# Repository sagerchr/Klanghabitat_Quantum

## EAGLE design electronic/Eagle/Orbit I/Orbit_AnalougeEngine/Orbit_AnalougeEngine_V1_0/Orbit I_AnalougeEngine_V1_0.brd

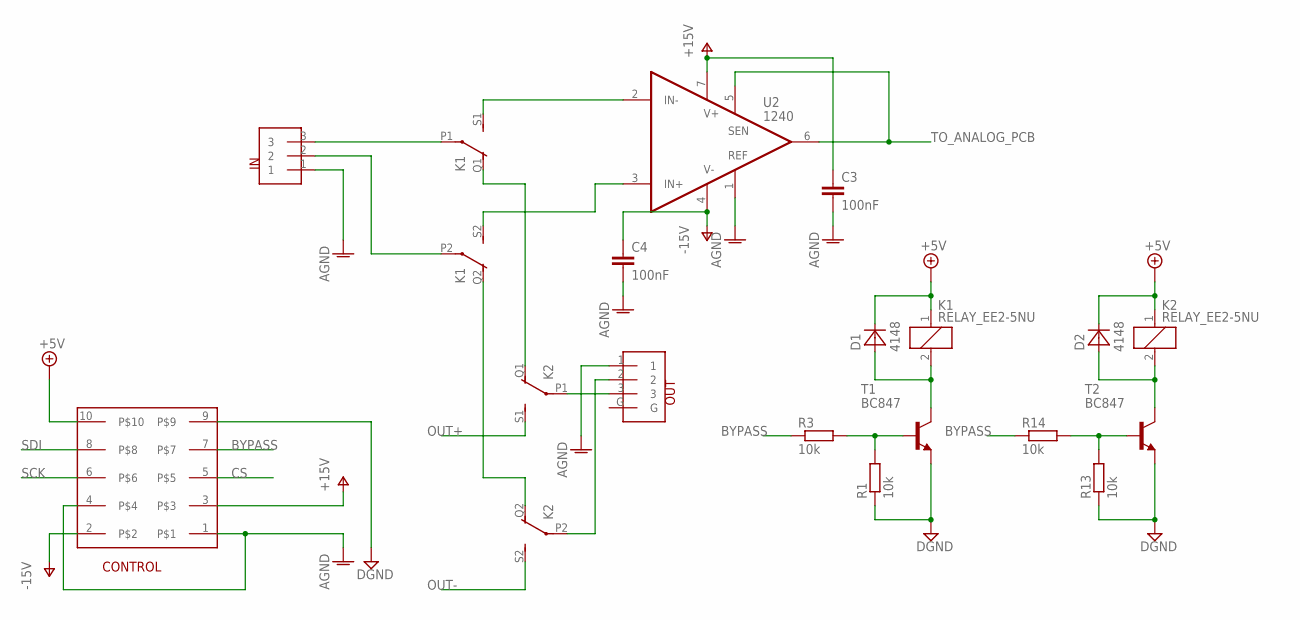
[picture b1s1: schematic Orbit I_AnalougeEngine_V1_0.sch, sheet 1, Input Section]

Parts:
C3, C4: 100nF; C0603
CONTROL: 10PIN_HEADER_SMD; 87832-10
D1, D2: 4148; SOD323-R
IN: NEUTRIK_NC3FAH
K1, K2: RELAY_EE2-5NU; 351
OUT: NEUTRIK_NC3MAH
R1, R3, R13, R14: 10k; R0805
T1, T2: BC847; SOT23
U2: 1240; SO08

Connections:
+5V: CONTROL.10, D1.C, D2.C, K1.1, K2.1
AGND: C3.2, C4.2, CONTROL.1, CONTROL.4, IN.1, OUT.1, U2.1 (REF); also elsewhere on the board
BYPASS: CONTROL.7, R3.1, R14.1
CS: CONTROL.5; also elsewhere on the board
DGND: CONTROL.9, R1.1, R13.1, T1.2 (E), T2.2 (E); also elsewhere on the board
unnamed: K1.S1 (S), U2.2 (IN-)
unnamed: K1.S2 (S), U2.3 (IN+)
unnamed: D2.A, K2.2, T2.3 (C)
unnamed: R13.2, R14.2, T2.1 (B)
unnamed: D1.A, K1.2, T1.3 (C)
unnamed: K1.Q1 (O), K2.Q1 (O)
unnamed: R1.2, R3.2, T1.1 (B)
unnamed: K1.Q2 (O), K2.Q2 (O)
unnamed: IN.2, K1.P2
unnamed: IN.3, K1.P1
unnamed: K2.P2, OUT.2
unnamed: K2.P1, OUT.3
OUT+: K2.S1 (S); also elsewhere on the board
OUT-: K2.S2 (S); also elsewhere on the board
SCK: CONTROL.6; also elsewhere on the board
SDI: CONTROL.8; also elsewhere on the board
TO_ANALOG_PCB: U2.5 (SEN), U2.6 (OUT); also elsewhere on the board
V+: C3.1, CONTROL.3, U2.7 (V+); also elsewhere on the board
V-: C4.1, CONTROL.2, U2.4 (V-); also elsewhere on the board

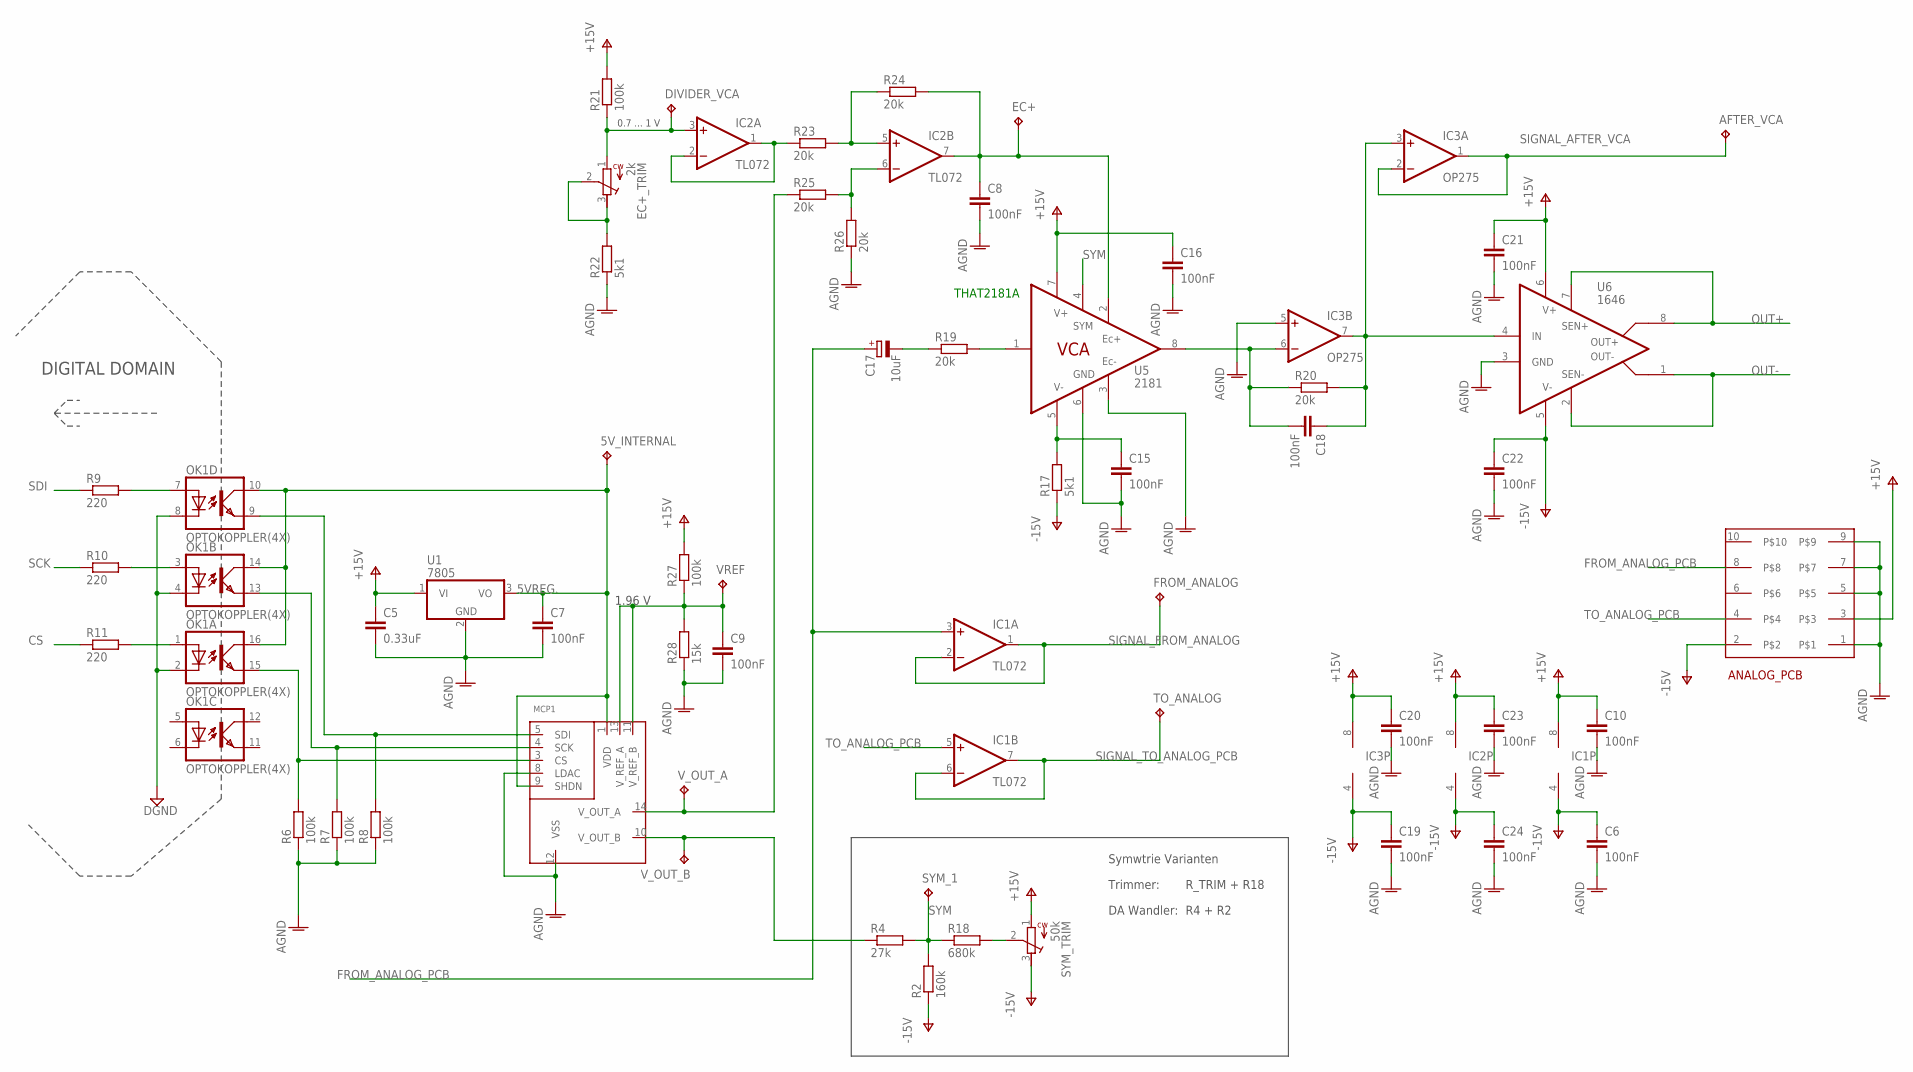
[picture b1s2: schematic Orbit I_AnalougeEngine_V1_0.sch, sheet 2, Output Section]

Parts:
5V_INTERNAL: TPTHT; THT_PIN
AFTER_VCA: TPTHT; THT_PIN
ANALOG_PCB: 10PIN_HEADER_SMD; 87832-10
C5: 0.33uF; C0603
C6, C7, C8, C9, C10, C15, C16, C18, C19, C20, C21, C22, C23, C24: 100nF; C0603
C17: 10uF; 153CLV-0605
DIVIDER_VCA: TPTHT; THT_PIN
EC+: TPTHT; THT_PIN
EC+_TRIM: 2k; RTRIM4G/J
FROM_ANALOG: TPTHT; THT_PIN
IC1, IC2: TL072; SOIC8
IC3: OP275; SOIC8
MCP1: MCP4922; SOIC16
OK1: OPTOKOPPLER(4X); SOIC16
R2: 160k; R0805
R4: 27k; R0805
R6, R7, R8, R21, R27: 100k; R0805
R9, R10, R11: 220; R0805
R17, R22: 5k1; R0805
R18: 680k; R0805
R19, R20, R23, R24, R25, R26: 20k; R0805
R28: 15k; R0805
SYM_1: TPTHT; THT_PIN
SYM_TRIM: 50k; RTRIM4G/J
TO_ANALOG: TPTHT; THT_PIN
U1: 7805; TO252
U5: 2181; SO08
U6: 1646; SO08
VREF: TPTHT; THT_PIN
V_OUT_A: TPTHT; THT_PIN
V_OUT_B: TPTHT; THT_PIN

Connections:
5VREG.: 5V_INTERNAL.P$1, C7.1, MCP1.1 (VDD), MCP1.9 (SHDN), OK1.10 (COL), OK1.14 (COL), OK1.16 (COL), U1.3 (VO)
AGND: ANALOG_PCB.1, ANALOG_PCB.5, ANALOG_PCB.7, ANALOG_PCB.9, C5.2, C6.2, C7.2, C8.2, C9.2, C10.2, C15.2, C16.2, C19.2, C20.2, C21.2, C22.2, C23.2, C24.2, IC3.5 (+IN), MCP1.8 (LDAC), MCP1.12 (VSS), R6.1, R7.1, R8.1, R22.1, R26.1, R28.1, U1.2 (GND), U5.3 (EC-), U5.6 (GND), U6.3 (GND); also elsewhere on the board
CS: R11.1; also elsewhere on the board
DGND: OK1.2 (C), OK1.4 (C), OK1.8 (C); also elsewhere on the board
FROM_ANALOG_PCB: ANALOG_PCB.8, C17.+, IC1.3 (+IN)
unnamed: C17.-, R19.1
unnamed: MCP1.3 (CS), OK1.15 (EMIT), R6.2
unnamed: MCP1.4 (SCK), OK1.13 (EMIT), R7.2
unnamed: MCP1.5 (SDI), OK1.9 (EMIT), R8.2
unnamed: OK1.7 (A), R9.2
unnamed: OK1.3 (A), R10.2
unnamed: OK1.1 (A), R11.2
unnamed: MCP1.10 (V_OUT_B), R4.1, V_OUT_B.P$1
unnamed: R18.2, SYM_TRIM.2
unnamed: C15.1, R17.2, U5.5 (V-)
unnamed: C18.2, IC3.6 (-IN), R20.1, U5.8 (OUT)
unnamed: C18.1, IC3.3 (+IN), IC3.7 (OUT), R20.2, U6.4 (IN)
unnamed: R19.2, U5.1 (IN)
unnamed: DIVIDER_VCA.P$1, EC+_TRIM.1, IC2.3 (+IN), R21.1
unnamed: IC2.1 (OUT), IC2.2 (-IN), R23.1
unnamed: IC2.5 (+IN), R23.2, R24.1
unnamed: C8.1, EC+.P$1, IC2.7 (OUT), R24.2, U5.2 (EC+)
unnamed: IC2.6 (-IN), R25.2, R26.2
unnamed: EC+_TRIM.2, EC+_TRIM.3, R22.2
unnamed: MCP1.14 (V_OUT_A), R25.1, V_OUT_A.P$1
unnamed: C9.1, MCP1.11 (V_REF_B), MCP1.13 (V_REF_A), R27.1, R28.2, VREF.P$1
OUT+: U6.7 (SEN+), U6.8 (OUT+); also elsewhere on the board
OUT-: U6.1 (OUT-), U6.2 (SEN-); also elsewhere on the board
SCK: R10.1; also elsewhere on the board
SDI: R9.1; also elsewhere on the board
SIGNAL_AFTER_VCA: AFTER_VCA.P$1, IC3.1 (OUT), IC3.2 (-IN)
SIGNAL_FROM_ANALOG: FROM_ANALOG.P$1, IC1.1 (OUT), IC1.2 (-IN)
SIGNAL_TO_ANALOG_PCB: IC1.6 (-IN), IC1.7 (OUT), TO_ANALOG.P$1
SYM: R2.2, R4.2, R18.1, SYM_1.P$1, U5.4 (SYM)
TO_ANALOG_PCB: ANALOG_PCB.4, IC1.5 (+IN); also elsewhere on the board
V+: ANALOG_PCB.3, C5.1, C10.1, C16.1, C20.1, C21.1, C23.1, IC1.8 (V+), IC2.8 (V+), IC3.8 (V+), R21.2, R27.2, SYM_TRIM.1, U1.1 (VI), U5.7 (V+), U6.6 (V+); also elsewhere on the board
V-: ANALOG_PCB.2, C6.1, C19.1, C22.1, C24.1, IC1.4 (V-), IC2.4 (V-), IC3.4 (V-), R2.1, R17.1, SYM_TRIM.3, U6.5 (V-); also elsewhere on the board

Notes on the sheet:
THAT2181A
0.7 ... 1 V
1.96 V
DIGITAL DOMAIN
Symwtrie Varianten
Trimmer:
R_TRIM + R18
DA Wandler:
R4 + R2

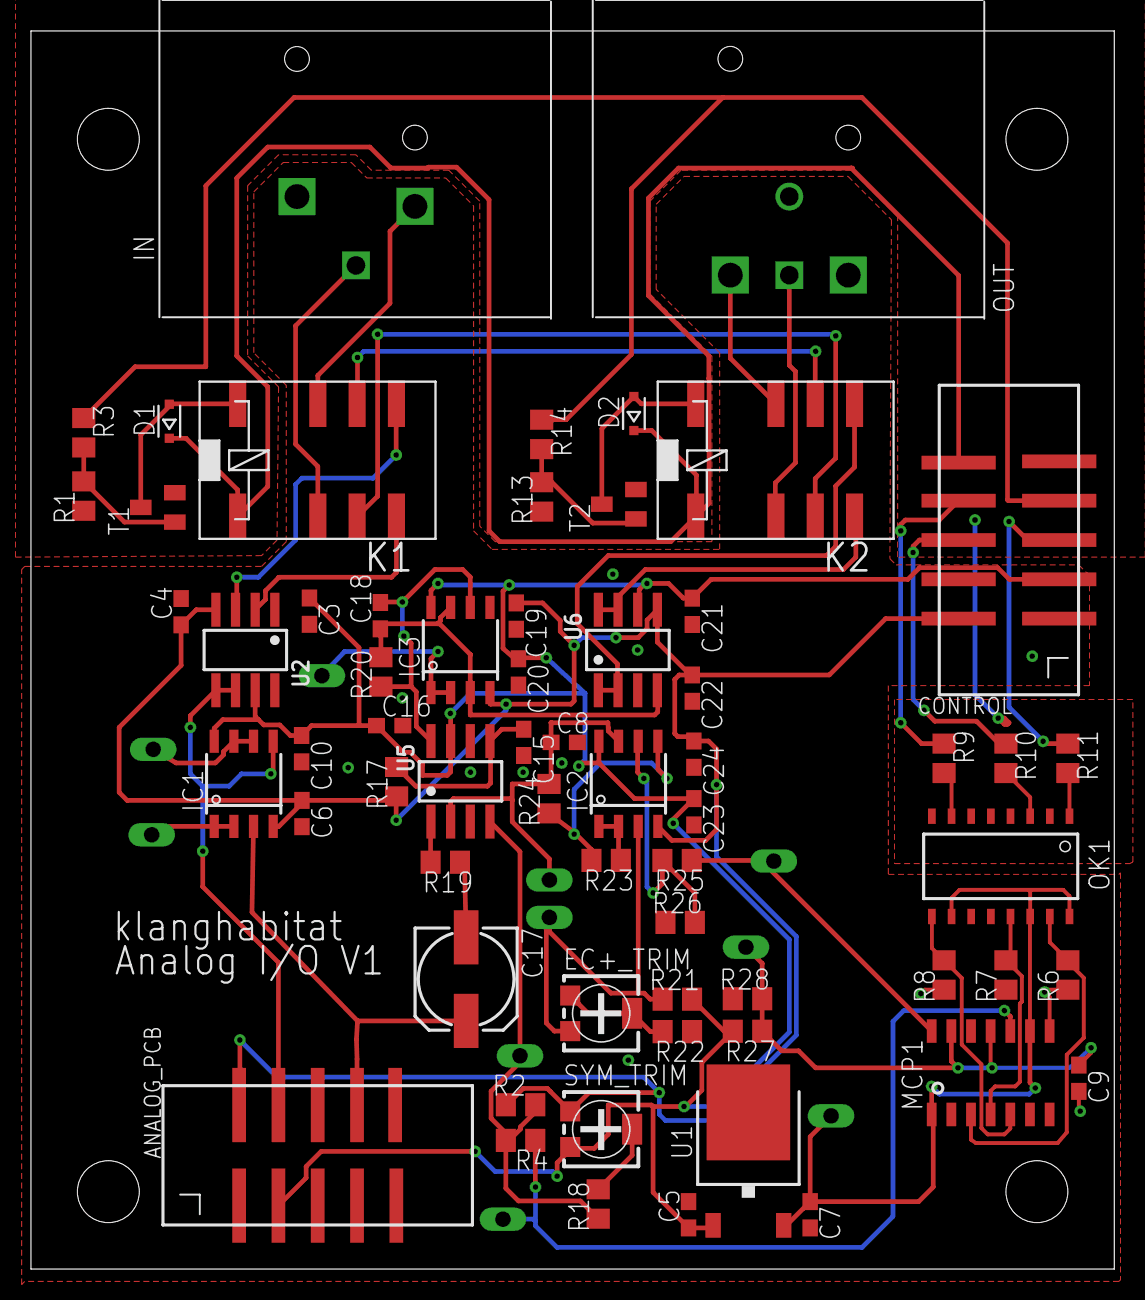
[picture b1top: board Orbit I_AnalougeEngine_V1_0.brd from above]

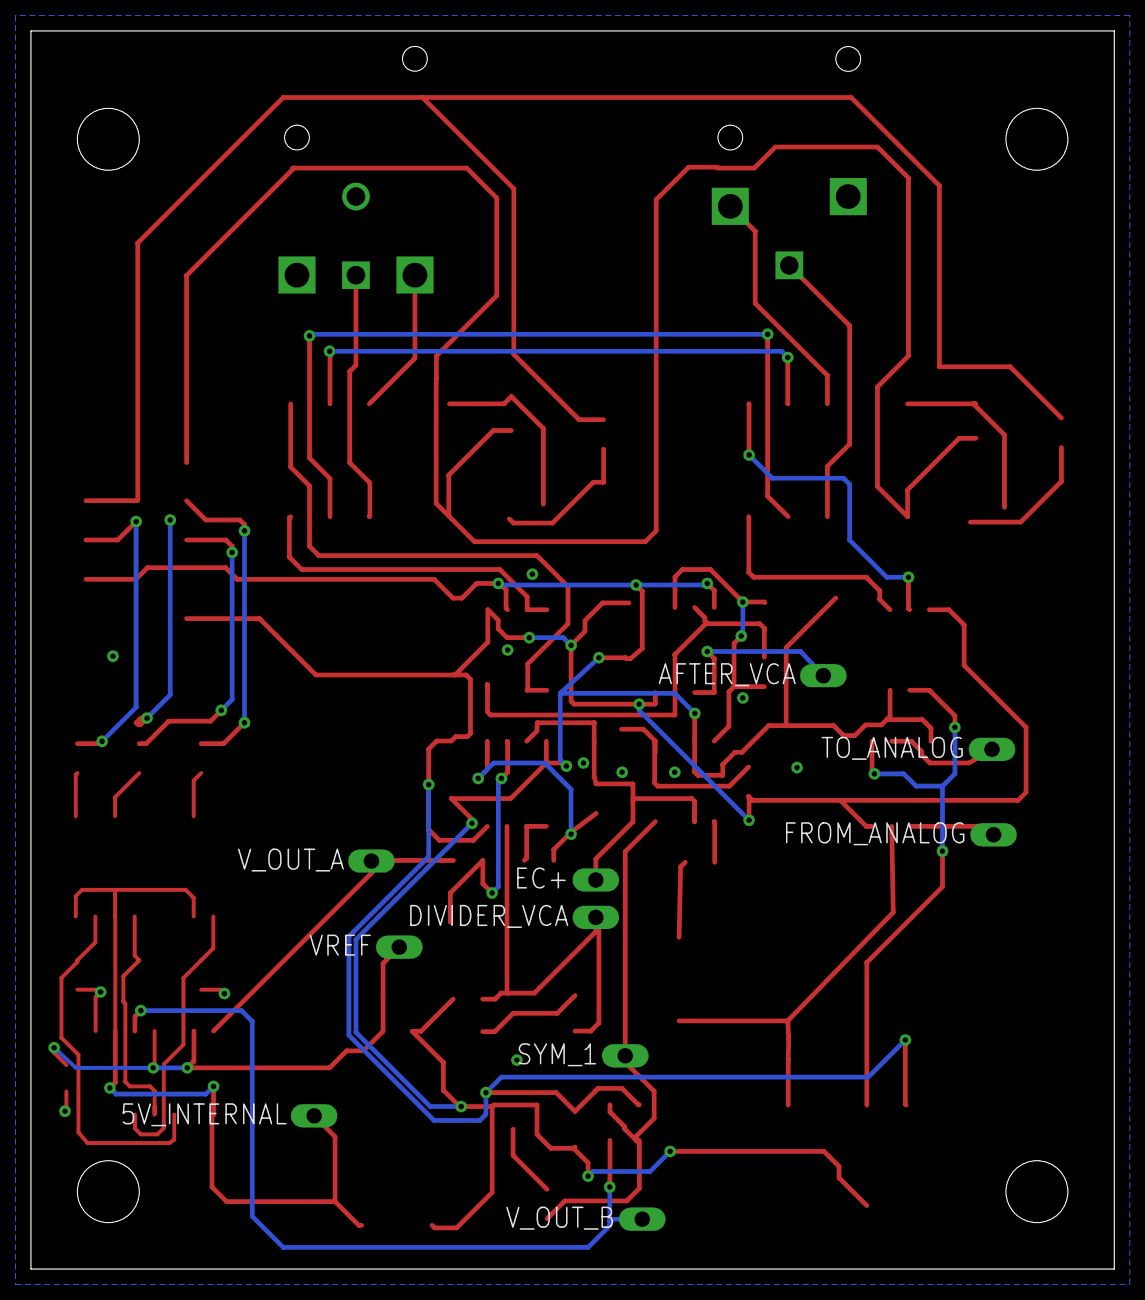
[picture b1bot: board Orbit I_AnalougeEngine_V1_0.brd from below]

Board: 2 copper layers, 70.0 x 80.0 mm, 73 parts (10 on the bottom side), 51 nets.

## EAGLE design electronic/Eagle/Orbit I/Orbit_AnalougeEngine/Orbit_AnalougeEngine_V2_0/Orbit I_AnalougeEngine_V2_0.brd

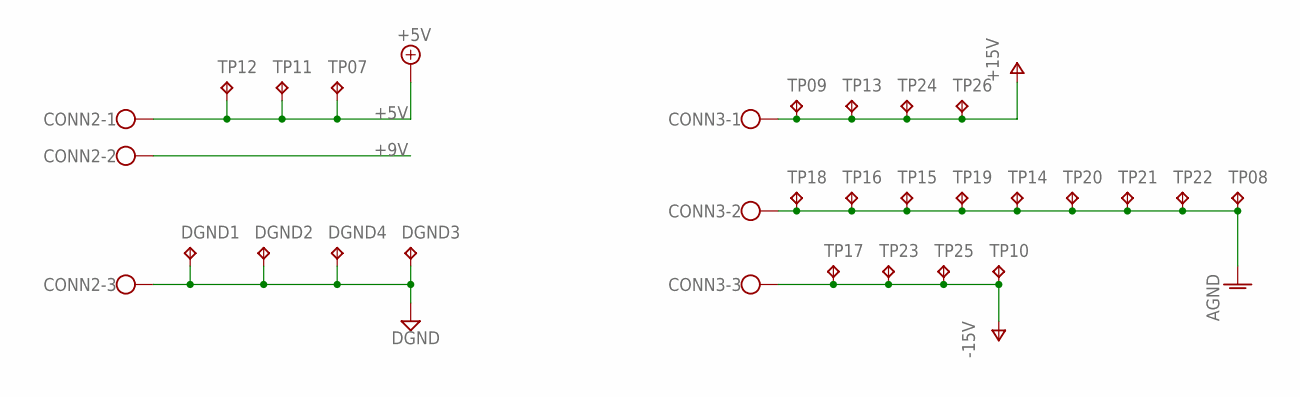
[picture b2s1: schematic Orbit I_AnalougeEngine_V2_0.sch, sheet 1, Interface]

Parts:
CONN2, CONN3: SCHRAUBKLEMME_3POL; W237-103
DGND1, DGND2, DGND3, DGND4: TPTHT; THT_PIN
TP07, TP08, TP09, TP10, TP11, TP12, TP13, TP14, TP15, TP16, TP17, TP18, TP19, TP20, TP21, TP22, TP23, TP24, TP25, TP26: TPTHT; THT_PIN

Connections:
+5V: CONN2.1, TP07.P$1, TP11.P$1, TP12.P$1; also elsewhere on the board
+9V: CONN2.2
AGND: CONN3.2, TP08.P$1, TP14.P$1, TP15.P$1, TP16.P$1, TP18.P$1, TP19.P$1, TP20.P$1, TP21.P$1, TP22.P$1; also elsewhere on the board
DGND: CONN2.3, DGND1.P$1, DGND2.P$1, DGND3.P$1, DGND4.P$1; also elsewhere on the board
V+: CONN3.1, TP09.P$1, TP13.P$1, TP24.P$1, TP26.P$1; also elsewhere on the board
V-: CONN3.3, TP10.P$1, TP17.P$1, TP23.P$1, TP25.P$1; also elsewhere on the board

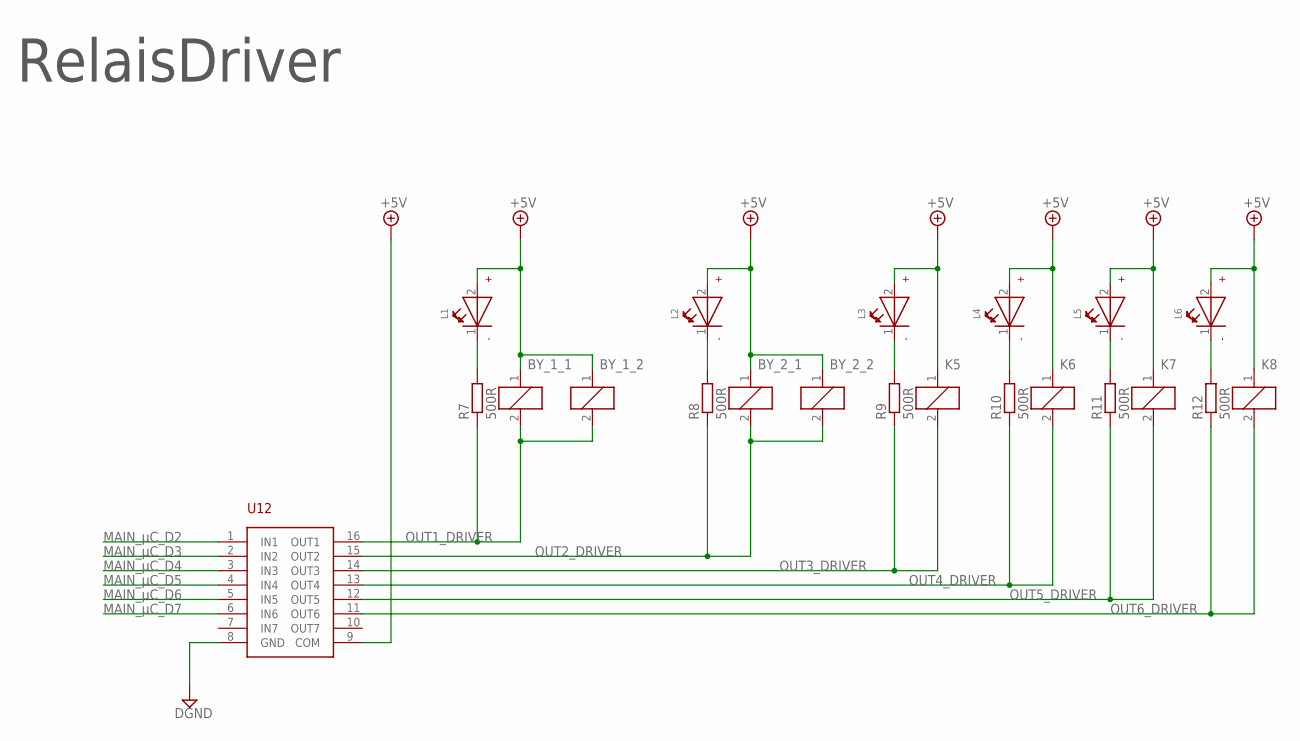
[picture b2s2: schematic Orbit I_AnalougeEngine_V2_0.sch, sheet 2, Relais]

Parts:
BY_1_1, BY_1_2, BY_2_1, BY_2_2: RELAY_EE2-5NU; 351
K5, K6, K7, K8: RELAY_EE2-5NU; 351
L1, L2, L3, L4, L5, L6: SMD_LED_0603; WL-SMCW_0603
R7, R8, R9, R10, R11, R12: 500R; R0805
U12: ULN2003; SOIC16

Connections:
+5V: BY_1_1.1, BY_1_2.1, BY_2_1.1, BY_2_2.1, K5.1, K6.1, K7.1, K8.1, L1.2 (+), L2.2 (+), L3.2 (+), L4.2 (+), L5.2 (+), L6.2 (+), U12.9 (COM); also elsewhere on the board
DGND: U12.8 (GND); also elsewhere on the board
MAIN_µC_D2: U12.1 (IN1); also elsewhere on the board
MAIN_µC_D3: U12.2 (IN2); also elsewhere on the board
MAIN_µC_D4: U12.3 (IN3); also elsewhere on the board
MAIN_µC_D5: U12.4 (IN4); also elsewhere on the board
MAIN_µC_D6: U12.5 (IN5); also elsewhere on the board
MAIN_µC_D7: U12.6 (IN6); also elsewhere on the board
unnamed: L1.1 (-), R7.2
unnamed: L2.1 (-), R8.2
unnamed: L6.1 (-), R12.2
unnamed: L5.1 (-), R11.2
unnamed: L4.1 (-), R10.2
unnamed: L3.1 (-), R9.2
OUT1_DRIVER: BY_1_1.2, BY_1_2.2, R7.1, U12.16 (OUT1)
OUT2_DRIVER: BY_2_1.2, BY_2_2.2, R8.1, U12.15 (OUT2)
OUT3_DRIVER: K5.2, R9.1, U12.14 (OUT3)
OUT4_DRIVER: K6.2, R10.1, U12.13 (OUT4)
OUT5_DRIVER: K7.2, R11.1, U12.12 (OUT5)
OUT6_DRIVER: K8.2, R12.1, U12.11 (OUT6)

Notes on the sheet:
RelaisDriver

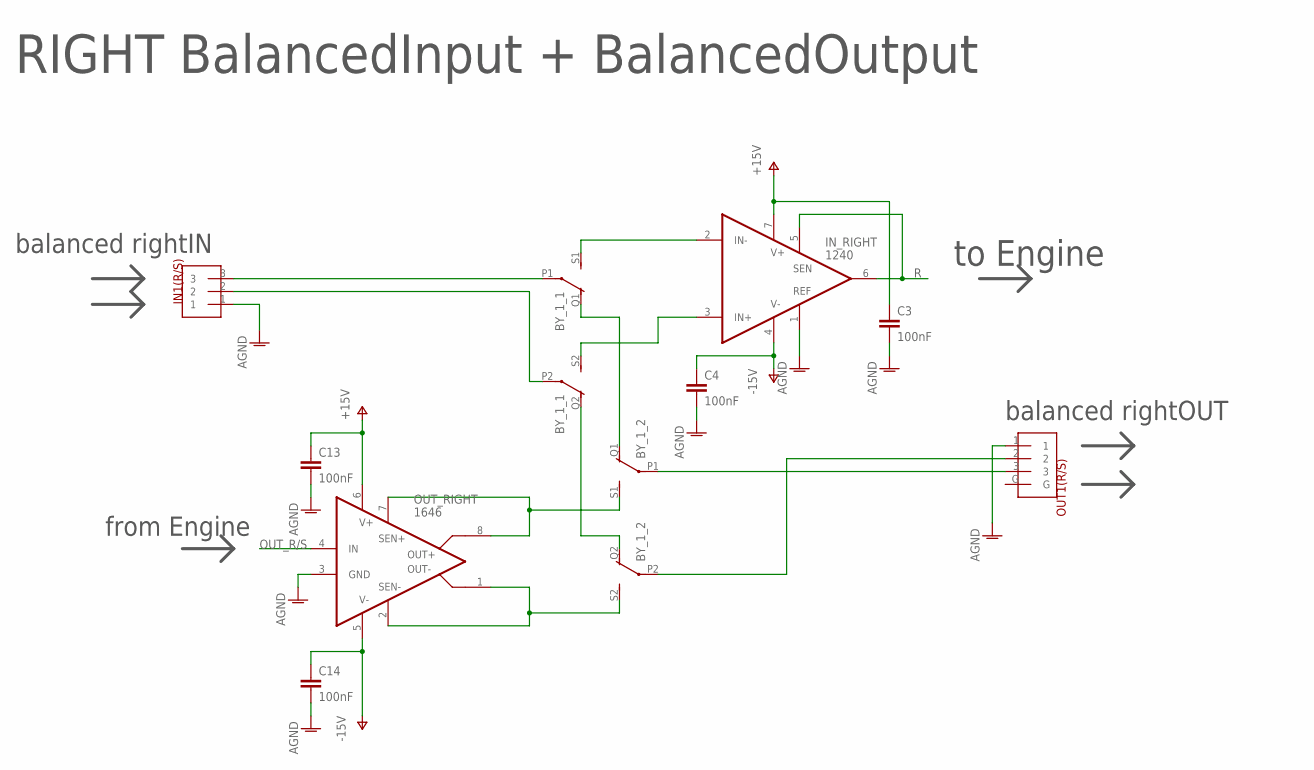
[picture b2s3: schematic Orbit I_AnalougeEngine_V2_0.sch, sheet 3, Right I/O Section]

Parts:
BY_1_1, BY_1_2: RELAY_EE2-5NU; 351
C3, C4, C13, C14: 100nF; C0603
IN1(R/S): NEUTRIK_NC3FAH
IN_RIGHT: 1240; SO08
OUT1(R/S): NEUTRIK_NC3MAH
OUT_RIGHT: 1646; SO08

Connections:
AGND: C3.2, C4.2, C13.2, C14.2, IN1(R/S).1, IN_RIGHT.1 (REF), OUT1(R/S).1, OUT_RIGHT.3 (GND); also elsewhere on the board
unnamed: BY_1_1.S1 (S), IN_RIGHT.2 (IN-)
unnamed: BY_1_1.S2 (S), IN_RIGHT.3 (IN+)
unnamed: BY_1_1.Q1 (O), BY_1_2.Q1 (O)
unnamed: BY_1_1.Q2 (O), BY_1_2.Q2 (O)
unnamed: BY_1_1.P2, IN1(R/S).2
unnamed: BY_1_1.P1, IN1(R/S).3
unnamed: BY_1_2.P2, OUT1(R/S).2
unnamed: BY_1_2.P1, OUT1(R/S).3
OUT_R/S: OUT_RIGHT.4 (IN); also elsewhere on the board
R: IN_RIGHT.5 (SEN), IN_RIGHT.6 (OUT); also elsewhere on the board
R/S_OUT+: BY_1_2.S1 (S), OUT_RIGHT.7 (SEN+), OUT_RIGHT.8 (OUT+)
R/S_OUT-: BY_1_2.S2 (S), OUT_RIGHT.1 (OUT-), OUT_RIGHT.2 (SEN-)
V+: C3.1, C13.1, IN_RIGHT.7 (V+), OUT_RIGHT.6 (V+); also elsewhere on the board
V-: C4.1, C14.1, IN_RIGHT.4 (V-), OUT_RIGHT.5 (V-); also elsewhere on the board

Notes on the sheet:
RIGHT BalancedInput + BalancedOutput
balanced rightIN
balanced rightOUT
from Engine
to Engine

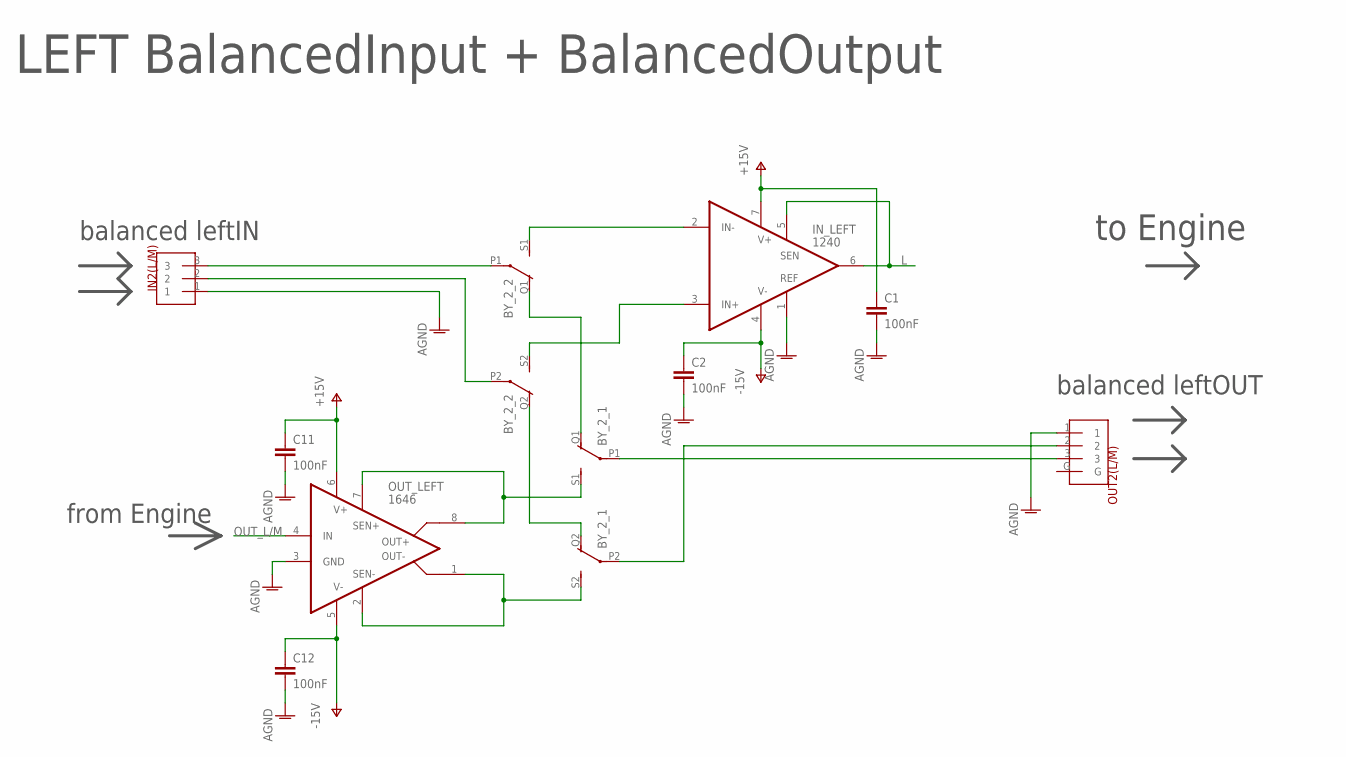
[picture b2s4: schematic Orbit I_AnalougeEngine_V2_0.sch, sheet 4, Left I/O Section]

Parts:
BY_2_1, BY_2_2: RELAY_EE2-5NU; 351
C1, C2, C11, C12: 100nF; C0603
IN2(L/M): NEUTRIK_NC3FAH
IN_LEFT: 1240; SO08
OUT2(L/M): NEUTRIK_NC3MAH
OUT_LEFT: 1646; SO08

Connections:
AGND: C1.2, C2.2, C11.2, C12.2, IN2(L/M).1, IN_LEFT.1 (REF), OUT2(L/M).1, OUT_LEFT.3 (GND); also elsewhere on the board
L: IN_LEFT.5 (SEN), IN_LEFT.6 (OUT); also elsewhere on the board
L/M_OUT+: BY_2_1.S1 (S), OUT_LEFT.7 (SEN+), OUT_LEFT.8 (OUT+)
L/M_OUT-: BY_2_1.S2 (S), OUT_LEFT.1 (OUT-), OUT_LEFT.2 (SEN-)
unnamed: BY_2_2.S2 (S), IN_LEFT.3 (IN+)
unnamed: BY_2_2.S1 (S), IN_LEFT.2 (IN-)
unnamed: BY_2_1.P1, OUT2(L/M).3
unnamed: BY_2_1.P2, OUT2(L/M).2
unnamed: BY_2_2.P1, IN2(L/M).3
unnamed: BY_2_2.P2, IN2(L/M).2
unnamed: BY_2_1.Q1 (O), BY_2_2.Q1 (O)
unnamed: BY_2_1.Q2 (O), BY_2_2.Q2 (O)
OUT_L/M: OUT_LEFT.4 (IN); also elsewhere on the board
V+: C1.1, C11.1, IN_LEFT.7 (V+), OUT_LEFT.6 (V+); also elsewhere on the board
V-: C2.1, C12.1, IN_LEFT.4 (V-), OUT_LEFT.5 (V-); also elsewhere on the board

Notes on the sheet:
balanced leftIN
balanced leftOUT
from Engine
to Engine
LEFT BalancedInput + BalancedOutput

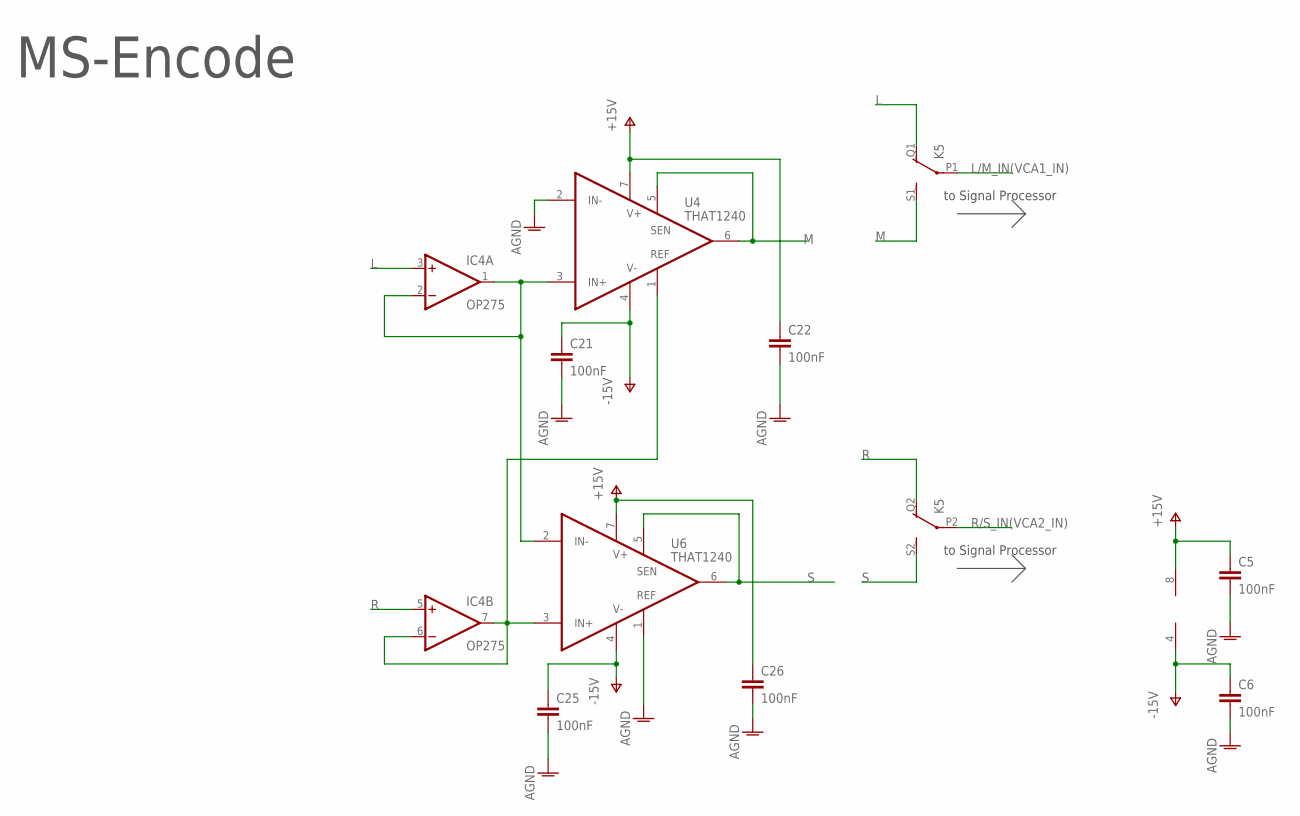
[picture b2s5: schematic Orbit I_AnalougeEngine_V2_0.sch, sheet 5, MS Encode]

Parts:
C5, C6, C21, C22, C25, C26: 100nF; C0603
IC4: OP275; SOIC8
K5: RELAY_EE2-5NU; 351
U4, U6: THAT1240; SO08

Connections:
AGND: C5.2, C6.2, C21.2, C22.2, C25.2, C26.2, U4.2 (IN-), U6.1 (REF); also elsewhere on the board
L: IC4.3 (+IN), K5.Q1 (O); also elsewhere on the board
L/M_IN(VCA1_IN): K5.P1; also elsewhere on the board
M: K5.S1 (S), U4.5 (SEN), U4.6 (OUT); also elsewhere on the board
unnamed: IC4.1 (OUT), IC4.2 (-IN), U4.3 (IN+), U6.2 (IN-)
unnamed: IC4.6 (-IN), IC4.7 (OUT), U4.1 (REF), U6.3 (IN+)
R: IC4.5 (+IN), K5.Q2 (O); also elsewhere on the board
R/S_IN(VCA2_IN): K5.P2; also elsewhere on the board
S: K5.S2 (S), U6.5 (SEN), U6.6 (OUT); also elsewhere on the board
V+: C5.1, C22.1, C26.1, IC4.8 (V+), U4.7 (V+), U6.7 (V+); also elsewhere on the board
V-: C6.1, C21.1, C25.1, IC4.4 (V-), U4.4 (V-), U6.4 (V-); also elsewhere on the board

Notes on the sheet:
to Signal Processor
MS-Encode

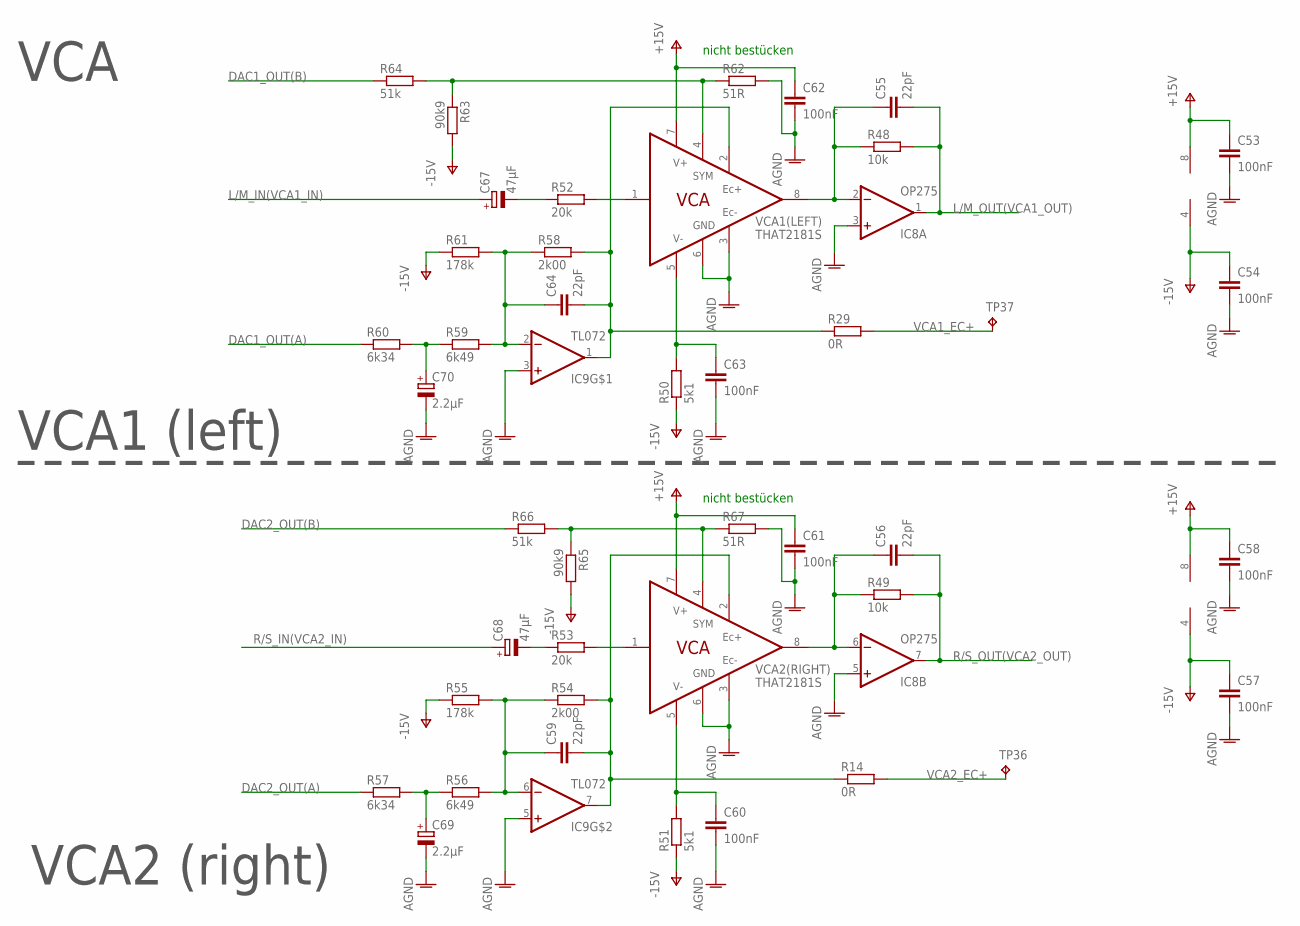
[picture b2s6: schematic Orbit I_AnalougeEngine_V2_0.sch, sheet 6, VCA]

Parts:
C53, C54, C57, C58, C60, C61, C62, C63: 100nF; C0603
C55, C56, C59, C64: 22pF; C0603
C67, C68: 47µF; 153CLV-0605
C69, C70: 2.2µF; 153CLV-0605
IC8: OP275; SOIC8
IC9: TL072; SOIC8
R14, R29: 0R; R0805
R48, R49: 10k; R0805
R50, R51: 5k1; R0805
R52, R53: 20k; R0805
R54, R58: 2k00; R0805
R55, R61: 178k; R0805
R56, R59: 6k49; R0805
R57, R60: 6k34; R0805
R62, R67: 51R; R0805
R63, R65: 90k9; R0805
R64, R66: 51k; R0805
TP36, TP37: TPTHT; THT_PIN
VCA1(LEFT), VCA2(RIGHT): THAT2181S; SO08

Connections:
AGND: C53.2, C54.2, C57.2, C58.2, C60.2, C61.2, C62.2, C63.2, C69.-, C70.-, IC8.3 (+IN), IC8.5 (+IN), IC9.3 (+IN), IC9.5 (+IN), R62.2, R67.2, VCA1(LEFT).3 (EC-), VCA1(LEFT).6 (GND), VCA2(RIGHT).3 (EC-), VCA2(RIGHT).6 (GND); also elsewhere on the board
DAC1_OUT(A): R60.1; also elsewhere on the board
DAC1_OUT(B): R64.1; also elsewhere on the board
DAC2_OUT(A): R57.1; also elsewhere on the board
DAC2_OUT(B): R66.1; also elsewhere on the board
L/M_IN(VCA1_IN): C67.+; also elsewhere on the board
L/M_OUT(VCA1_OUT): C55.2, IC8.1 (OUT), R48.2; also elsewhere on the board
unnamed: C55.1, IC8.2 (-IN), R48.1, VCA1(LEFT).8 (OUT)
unnamed: R52.2, VCA1(LEFT).1 (IN)
unnamed: C67.-, R52.1
unnamed: C70.+, R59.1, R60.2
unnamed: C56.1, IC8.6 (-IN), R49.1, VCA2(RIGHT).8 (OUT)
unnamed: C60.1, R51.2, VCA2(RIGHT).5 (V-)
unnamed: C68.-, R53.1
unnamed: R53.2, VCA2(RIGHT).1 (IN)
unnamed: C63.1, R50.2, VCA1(LEFT).5 (V-)
unnamed: C59.1, IC9.6 (-IN), R54.1, R55.2, R56.2
unnamed: C59.2, IC9.7 (OUT), R14.1, R54.2, VCA2(RIGHT).2 (EC+)
unnamed: C64.1, IC9.2 (-IN), R58.1, R59.2, R61.2
unnamed: C69.+, R56.1, R57.2
unnamed: R62.1, R63.1, R64.2, VCA1(LEFT).4 (SYM)
unnamed: C64.2, IC9.1 (OUT), R29.1, R58.2, VCA1(LEFT).2 (EC+)
unnamed: R65.1, R66.2, R67.1, VCA2(RIGHT).4 (SYM)
R/S_IN(VCA2_IN): C68.+; also elsewhere on the board
R/S_OUT(VCA2_OUT): C56.2, IC8.7 (OUT), R49.2; also elsewhere on the board
V+: C53.1, C58.1, C61.1, C62.1, IC8.8 (V+), IC9.8 (V+), VCA1(LEFT).7 (V+), VCA2(RIGHT).7 (V+); also elsewhere on the board
V-: C54.1, C57.1, IC8.4 (V-), IC9.4 (V-), R50.1, R51.1, R55.1, R61.1, R63.2, R65.2; also elsewhere on the board
VCA1_EC+: R29.2, TP37.P$1; also elsewhere on the board
VCA2_EC+: R14.2, TP36.P$1; also elsewhere on the board

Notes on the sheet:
VCA
VCA1 (left)
VCA2 (right)
nicht bestücken

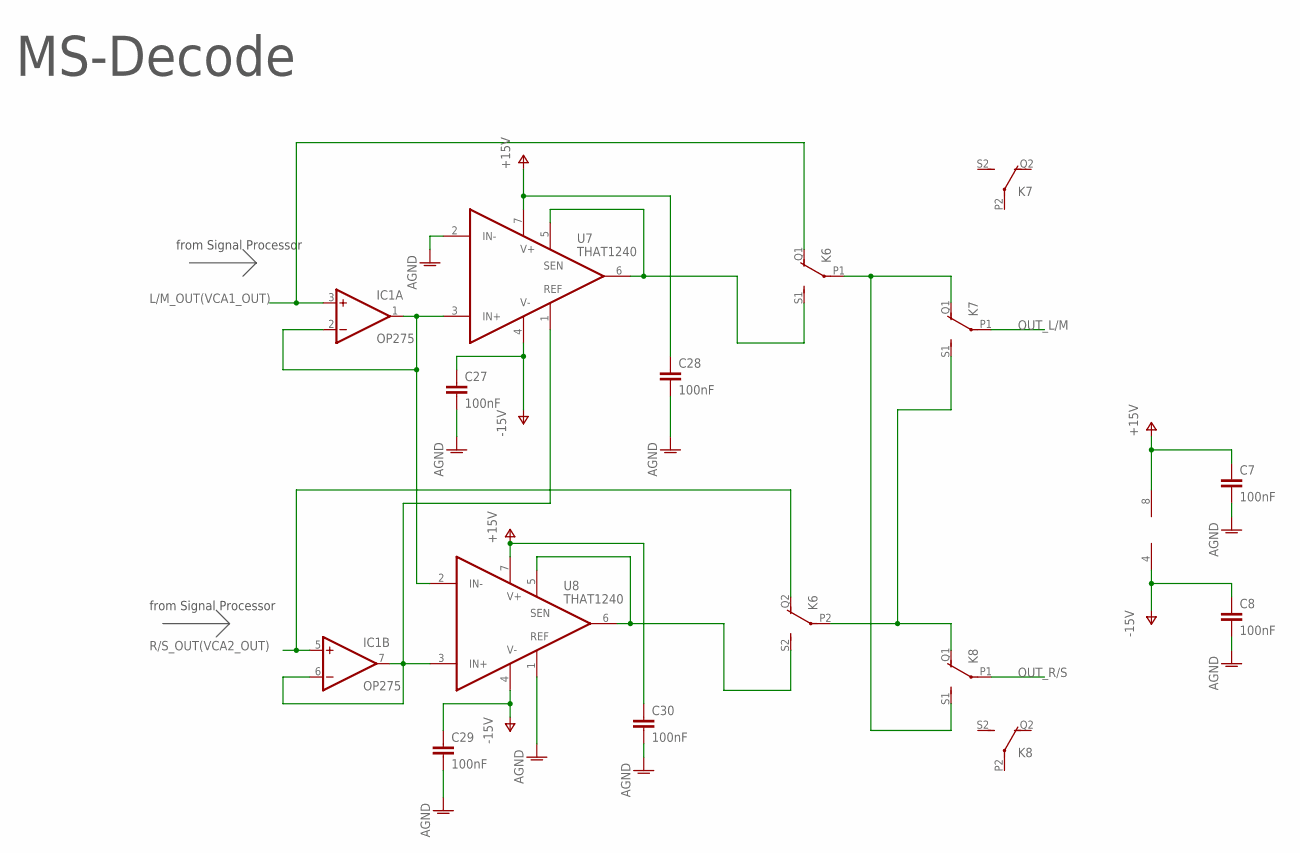
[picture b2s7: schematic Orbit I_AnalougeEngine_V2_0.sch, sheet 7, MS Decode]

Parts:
C7, C8, C27, C28, C29, C30: 100nF; C0603
IC1: OP275; SOIC8
K6, K7, K8: RELAY_EE2-5NU; 351
U7, U8: THAT1240; SO08

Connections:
AGND: C7.2, C8.2, C27.2, C28.2, C29.2, C30.2, U7.2 (IN-), U8.1 (REF); also elsewhere on the board
L/M_OUT(VCA1_OUT): IC1.3 (+IN), K6.Q1 (O); also elsewhere on the board
M1: K6.S1 (S), U7.5 (SEN), U7.6 (OUT)
unnamed: K6.P1, K7.Q1 (O), K8.S1 (S)
unnamed: K6.P2, K7.S1 (S), K8.Q1 (O)
unnamed: IC1.6 (-IN), IC1.7 (OUT), U7.1 (REF), U8.3 (IN+)
unnamed: IC1.1 (OUT), IC1.2 (-IN), U7.3 (IN+), U8.2 (IN-)
OUT_L/M: K7.P1; also elsewhere on the board
OUT_R/S: K8.P1; also elsewhere on the board
R/S_OUT(VCA2_OUT): IC1.5 (+IN), K6.Q2 (O); also elsewhere on the board
S1: K6.S2 (S), U8.5 (SEN), U8.6 (OUT)
V+: C7.1, C28.1, C30.1, IC1.8 (V+), U7.7 (V+), U8.7 (V+); also elsewhere on the board
V-: C8.1, C27.1, C29.1, IC1.4 (V-), U7.4 (V-), U8.4 (V-); also elsewhere on the board

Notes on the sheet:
from Signal Processor
MS-Decode
